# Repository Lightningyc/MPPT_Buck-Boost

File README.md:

&nbsp;&nbsp;

[English](./README.md)/中文

***
初赛演示视频：[2025年嵌入式设计大赛ST赛道-基于 STM32G4 平台的数控 MPPT 四开关 buckboost 变换器](https://www.bilibili.com/video/BV1HrGgzEE6s/)

# 作品实物图

# 1. 作品简介

## 1.1 关键性能指标
**输出电压：**
最高输出电压：10.74V

最低输出电压：15.20V

**稳态平均功率：**

12.39W

**稳态功率波动：**

0.02%

**最大功率点跟踪效率：**

94.8%
## 1.2 主要创新点

1. 双模式 MPPT 算法：结合 CV 法快速定位与 P&O 法动态跟踪，提高追
踪精度，加强了抗光照突变干扰能力。

2. 太阳能控制器硬件部分采用双板结构：控制板含 MCU 最小系统、采
样电路及调试接口；功率板集成主变换电路、驱动及滤波电路。全部设计基
于 KiCad 完成，兼顾调试便利与高低压隔离需求。

3. 使用 PSIM 仿真：充分利用 PSIM 仿真软件进行算法验证和参数优化，
实现了仿真与硬件开发的双线并行，提高了工作效率，还能提前发现潜在问
题，为后续硬件调试奠定了坚实基础。

# 2. 系统介绍

下图所示的太阳能控制器系统包含以下核心模块：DC-DC 电能变换电路、电压电流采样电路、输入输出滤波电路以及辅助电源电路。系统工作原理如下：

能量输入与处理：光伏电池板转换的太阳能电能，经输入滤波电路预处理后，输入至 DC-DC 变换电路。

状态监测：STM32G74 微控制器周期性采集经采样电路获取的输入/输出电压电流数据。

核心控制：微控制器对采集数据进行线性拟合，并运行内部 MPPT 算法，计算出控制指令。

功率调节：控制指令转化为PWM信号输出至栅极驱动器，驱动 DC-DC 变换电路的功率开关器件，从而动态调整其工作状态（如占空比），实现对输入或输出电参数的精准控制。

通信交互： 控制器通过 UART 接口与上位机软件 Vofa+ 通信，支持参数远程设定及实时运行数据（电压/电流）反馈。

安全保障与供电：

输入端设有防电流倒灌电路，防止能量逆向流动。

辅助电源电路集成提供 12V、5V 和 3.3V 的板级电源，为控制器内部所有模块稳定供电。

考虑到调试方便性以及高低压域分割问题，本文中的太阳能电池板控制器的硬件系统主要由控制部分与功率部分两块 PCB 板组合而成，其如图 2 所示，控制部分主要包括主控 MCU 最小系统、辅助电源、采样电路、调试接口和指示灯；功率部分主要包括电能变换主电路，输入输出滤波电路和栅极驱动电路。本作品的硬件全流程设计均基于 Kicad 软件。

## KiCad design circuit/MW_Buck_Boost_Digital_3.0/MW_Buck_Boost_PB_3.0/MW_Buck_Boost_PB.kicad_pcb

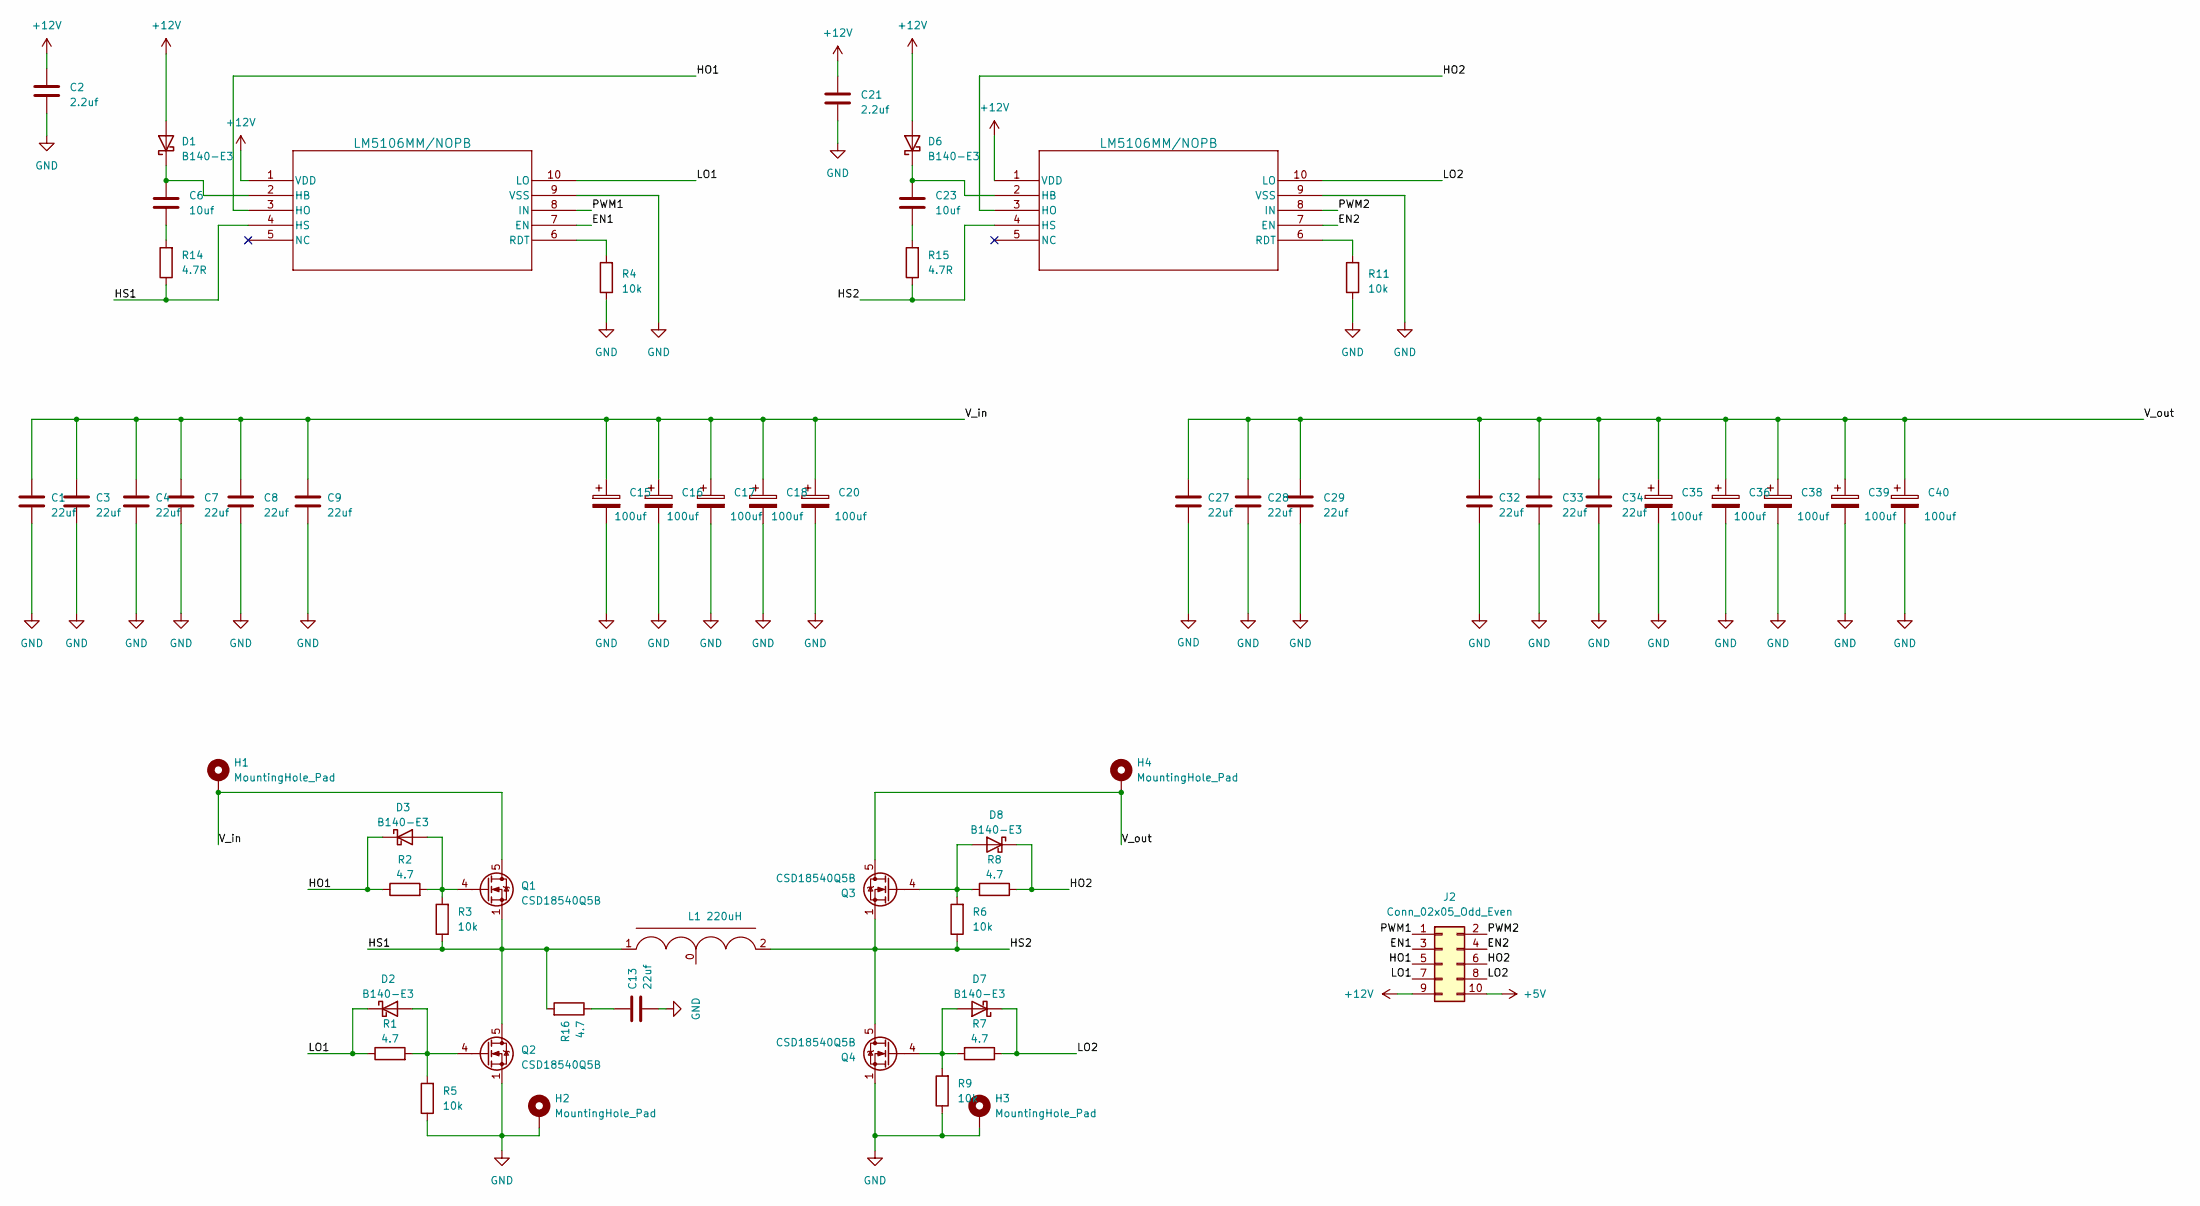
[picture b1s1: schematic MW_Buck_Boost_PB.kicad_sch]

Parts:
C1, C3, C4, C7, C8, C9, C13, C27, C28, C29, C32, C33, C34: 22uf; C_1206_3216Metric
C2, C21: 2.2uf; C_0603_1608Metric
C6, C23: 10uf; C_0603_1608Metric
C15, C16, C17, C18, C20, C35, C36, C38, C39, C40: 100uf; CP_Elec_8x10
D1, D2, D3, D6, D7, D8: B140-E3; D_SOD-123
H1, H2, H3, H4: MountingHole_Pad; MountingHole_3.2mm_M3_Pad_Via
J2: Conn_02x05_Odd_Even; PinHeader_2x05_P2.54mm_Vertical_SMD
L1: 220uH; L_Wurth_WE-HCFT-2012_LeadDiameter1.2mm
Q1, Q2, Q3, Q4: CSD18540Q5B; TDSON-8-1
R1, R2, R7, R8: 4.7; R_0603_1608Metric
R3, R4, R5, R6, R9, R11: 10k; R_0603_1608Metric
R14, R15: 4.7R; R_0603_1608Metric
R16: 4.7; R_1206_3216Metric
U1, U2: LM5106MM/NOPB; SOP50P490X110-10N

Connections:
+5V: J2.10
+12V: C2.1, C21.1, D1.2 (A), D6.2 (A), J2.9, U1.1 (VDD), U2.1 (VDD)
/EN1: J2.3, U1.7 (EN)
/EN2: J2.4, U2.7 (EN)
/HO1: D3.1 (K), J2.5, R2.1, U1.3 (HO)
/HO2: D8.1 (K), J2.6, R8.1, U2.3 (HO)
/HS1: L1.1, Q1.1 (S), Q1.2 (S), Q1.3 (S), Q2.5 (D), R3.1, R14.1, R16.2, U1.4 (HS)
/HS2: L1.2, Q3.1 (S), Q3.2 (S), Q3.3 (S), Q4.5 (D), R6.1, R15.1, U2.4 (HS)
/LO1: D2.1 (K), J2.7, R1.1, U1.10 (LO)
/LO2: D7.1 (K), J2.8, R7.1, U2.10 (LO)
/PWM1: J2.1, U1.8 (IN)
/PWM2: J2.2, U2.8 (IN)
/V_in: C1.1, C3.1, C4.1, C7.1, C8.1, C9.1, C15.1, C16.1, C17.1, C18.1, C20.1, H1.1, Q1.5 (D)
/V_out: C27.1, C28.1, C29.1, C32.1, C33.1, C34.1, C35.1, C36.1, C38.1, C39.1, C40.1, H4.1, Q3.5 (D)
GND: C1.2, C2.2, C3.2, C4.2, C7.2, C8.2, C9.2, C13.2, C15.2, C16.2, C17.2, C18.2, C20.2, C21.2, C27.2, C28.2, C29.2, C32.2, C33.2, C34.2, C35.2, C36.2, C38.2, C39.2, C40.2, H2.1, H3.1, Q2.1 (S), Q2.2 (S), Q2.3 (S), Q4.1 (S), Q4.2 (S), Q4.3 (S), R4.1, R5.1, R9.1, R11.1, U1.9 (VSS), U2.9 (VSS)
unnamed: C6.2, R14.2
unnamed: C13.1, R16.1
unnamed: C23.2, R15.2
unnamed: C6.1, D1.1 (K), U1.2 (HB)
unnamed: D2.2 (A), Q2.4 (G), R1.2, R5.2
unnamed: D3.2 (A), Q1.4 (G), R2.2, R3.2
unnamed: C23.1, D6.1 (K), U2.2 (HB)
unnamed: D7.2 (A), Q4.4 (G), R7.2, R9.2
unnamed: D8.2 (A), Q3.4 (G), R6.2, R8.2
unnamed: R4.2, U1.6 (RDT)
unnamed: R11.2, U2.6 (RDT)

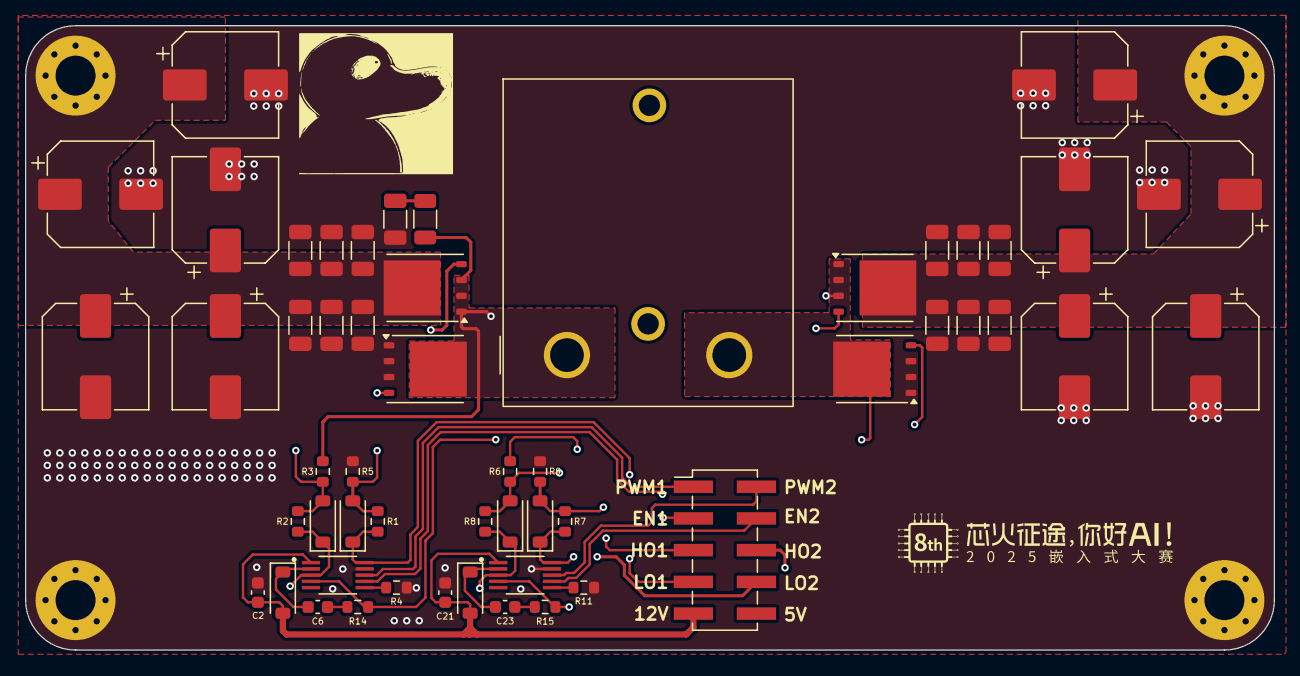
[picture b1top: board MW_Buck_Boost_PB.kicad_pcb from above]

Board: 4 copper layers, 100.0 x 50.0 mm, 58 parts (0 on the bottom side), 25 nets.

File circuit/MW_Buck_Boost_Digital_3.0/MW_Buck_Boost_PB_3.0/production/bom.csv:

Designator,Footprint,Quantity,Value,LCSC Part #
"C1, C13, C27, C28, C29, C3, C32, C33, C34, C4, C7, C8, C9",1206,13,22uf,
"C15, C16, C17, C18, C20, C35, C36, C38, C39, C40",CP_Elec_8x10,10,100uf,
"C2, C21",0603,2,2.2uf,
"C23, C6",0603,2,10uf,
"D1, D2, D3, D6, D7, D8",D_SOD-123,6,B140-E3,
"H1, H2, H3, H4",MountingHole_3.2mm_M3_Pad_Via,4,MountingHole_Pad,
J2,PinHeader_2x05_P2.54mm_Vertical_SMD,1,Conn_02x05_Odd_Even,
L1,L_Wurth_WE-HCFT-2012_LeadDiameter1.2mm,1,47uH,
"Q1, Q2, Q3, Q4",TDSON-8-1,4,CSD18540Q5B,
"R1, R2, R7, R8",0603,4,4.7,
"R11, R3, R4, R5, R6, R9",0603,6,10k,
"R14, R15",0603,2,4.7R,
R16,1206,1,4.7,
"U1, U2",SOP50P490X110-10N,2,LM5106MM/NOPB,

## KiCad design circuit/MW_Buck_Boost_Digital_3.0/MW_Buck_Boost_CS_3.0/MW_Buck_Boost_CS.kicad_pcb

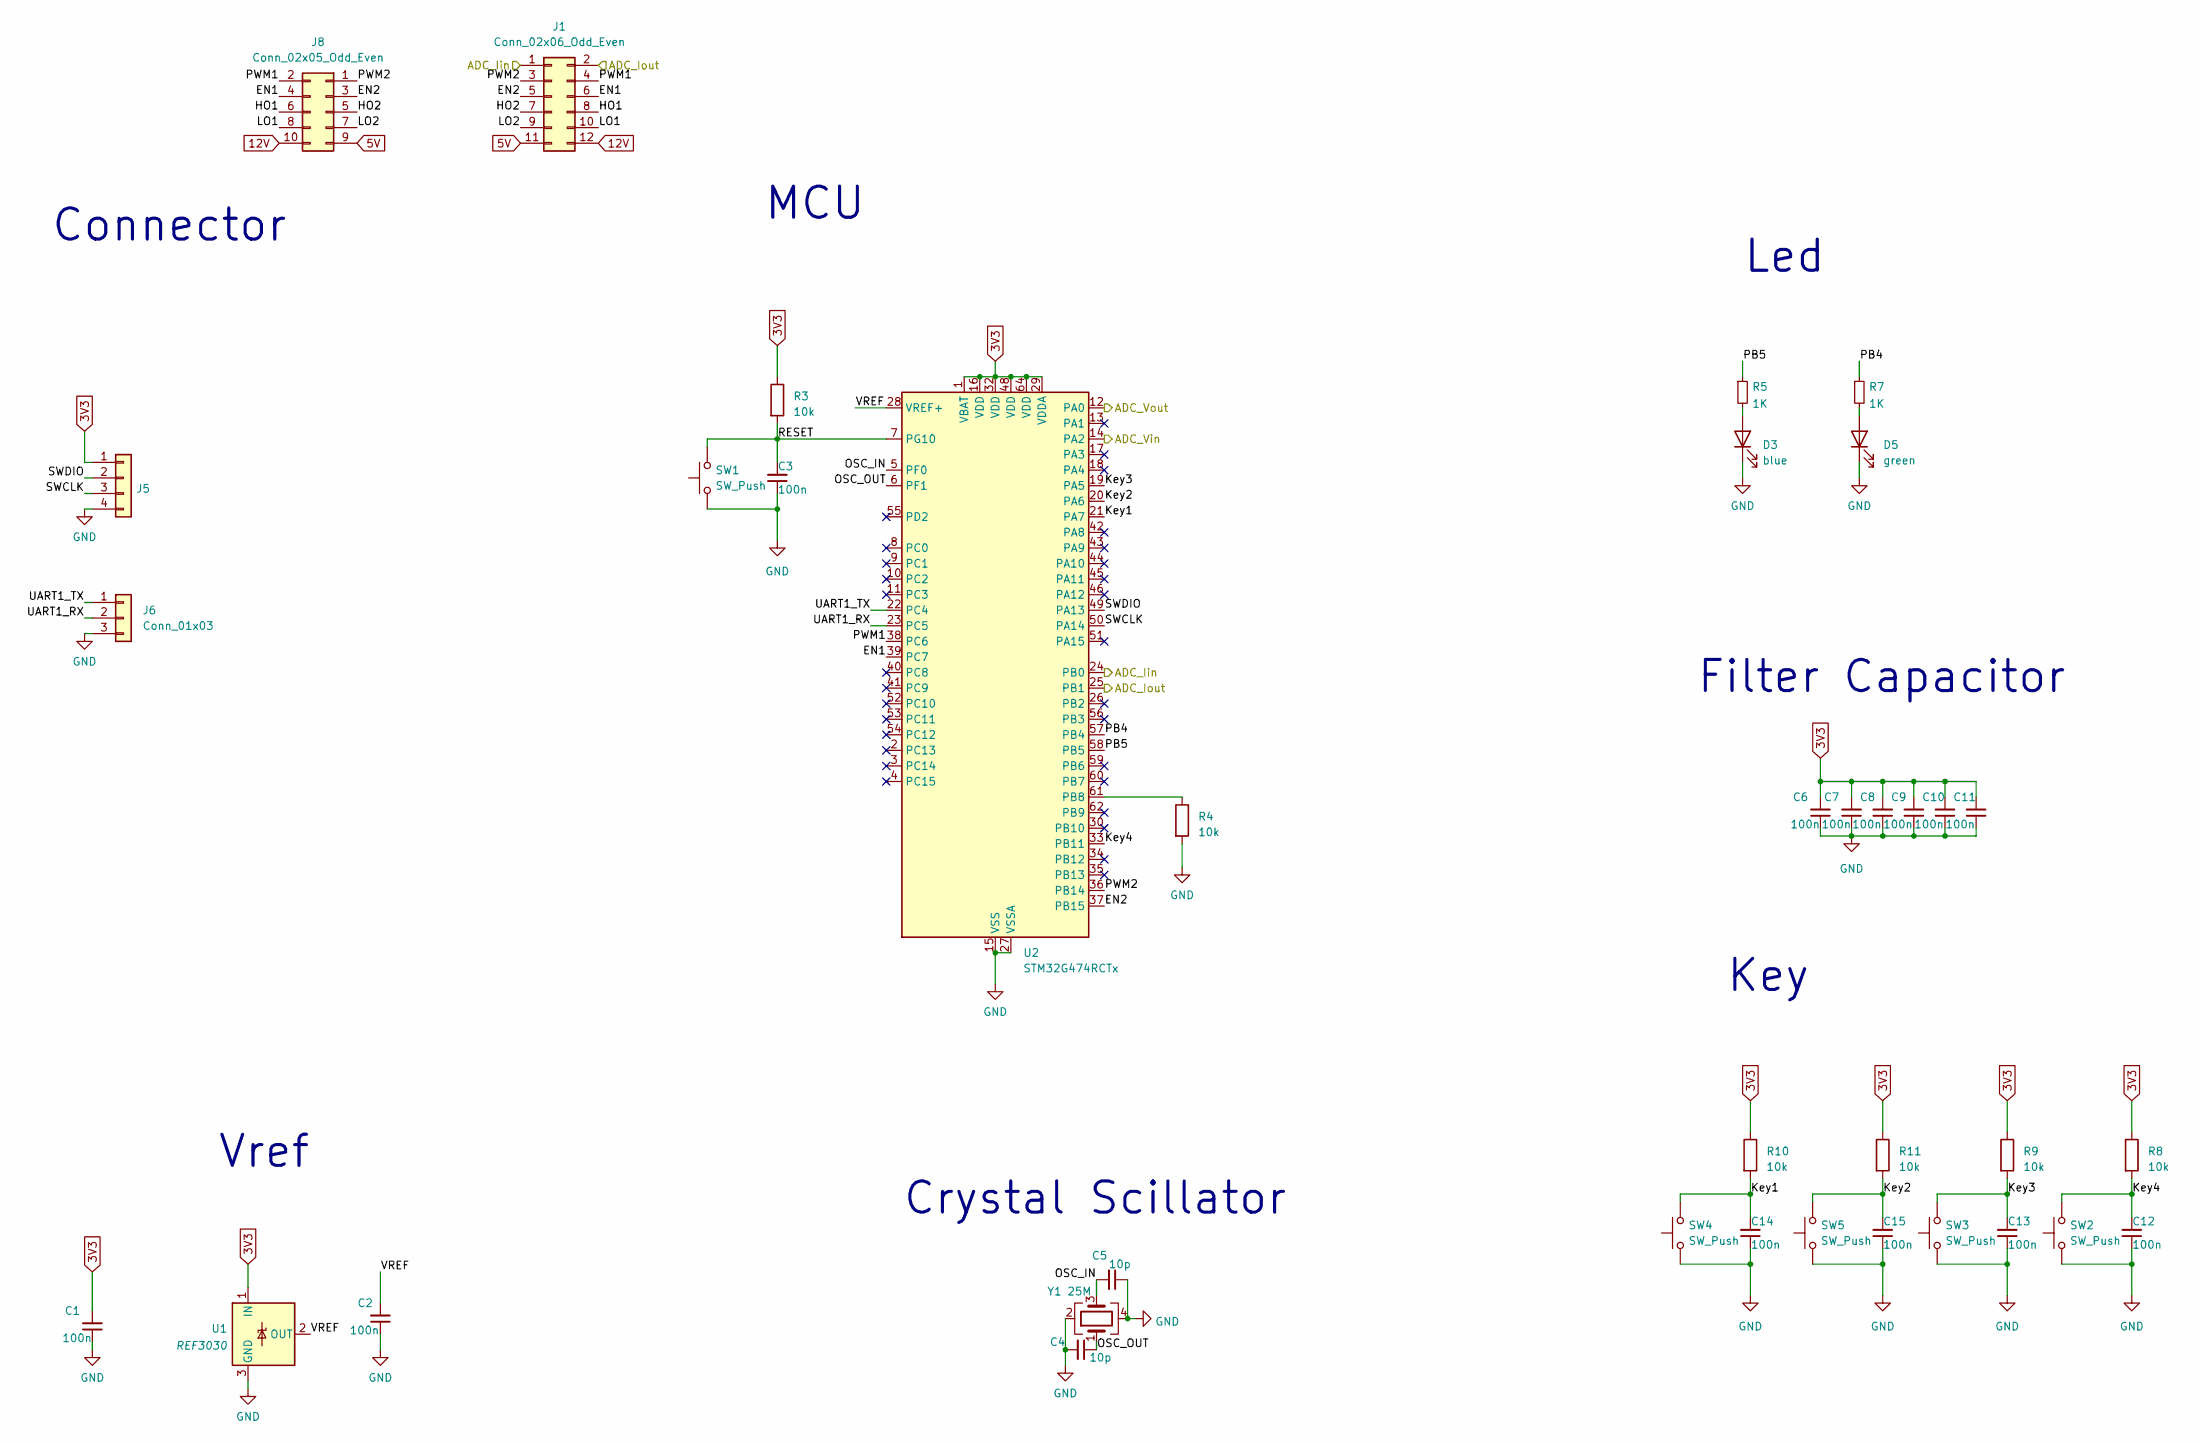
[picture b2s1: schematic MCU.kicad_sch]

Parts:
C1, C2, C3, C6, C7, C8, C9, C10, C11, C12, C13, C14, C15: 100n; C_0603_1608Metric_Pad1.08x0.95mm_HandSolder
C4, C5: 10p; C_0603_1608Metric_Pad1.08x0.95mm_HandSolder
D3: blue; LED_0603_1608Metric_Pad1.05x0.95mm_HandSolder
D5: green; LED_0603_1608Metric_Pad1.05x0.95mm_HandSolder
J1: Conn_02x06_Odd_Even; PinHeader_2x06_P2.54mm_Vertical_SMD
J5: Conn_01x04; JST_GH_SM04B-GHS-TB_1x04-1MP_P1.25mm_Horizontal
J6: Conn_01x03; JST_GH_SM03B-GHS-TB_1x03-1MP_P1.25mm_Horizontal
J8: Conn_02x05_Odd_Even; PinHeader_2x05_P2.54mm_Vertical_SMD
R3, R4, R8, R9, R10, R11: 10k; R_0603_1608Metric_Pad0.98x0.95mm_HandSolder
R5, R7: 1K; R_0603_1608Metric_Pad0.98x0.95mm_HandSolder
SW1, SW2, SW3, SW4, SW5: SW_Push; SW-SMD_4P-L4.2-W3.3-P2.15-LS5.1
U1: REF3030; SOT-23
U2: STM32G474RCTx; LQFP-64_10x10mm_P0.5mm
Y1: 25M; Crystal_SMD_3225-4Pin_3.2x2.5mm

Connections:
3V3: C1.2, C6.2, C7.2, C8.2, C9.2, C10.2, C11.2, J5.1, R3.1, R8.1, R9.1, R10.1, R11.1, U1.1 (IN), U2.1 (VBAT), U2.16 (VDD), U2.29 (VDDA), U2.32 (VDD), U2.48 (VDD), U2.64 (VDD); also elsewhere on the board
5V: J1.11, J8.9; also elsewhere on the board
12V: J1.12, J8.10; also elsewhere on the board
/MCU/ADC_Iin: J1.1, U2.24 (PB0); also elsewhere on the board
/MCU/ADC_Iout: J1.2, U2.25 (PB1); also elsewhere on the board
/MCU/ADC_Vin: U2.14 (PA2); also elsewhere on the board
/MCU/ADC_Vout: U2.12 (PA0); also elsewhere on the board
/MCU/EN1: J1.6, J8.4, U2.39 (PC7)
/MCU/EN2: J1.5, J8.3, U2.37 (PB15)
/MCU/HO1: J1.8, J8.6
/MCU/HO2: J1.7, J8.5
/MCU/Key1: C14.2, R10.2, SW4.2, U2.21 (PA7)
/MCU/Key2: C15.2, R11.2, SW5.2, U2.20 (PA6)
/MCU/Key3: C13.2, R9.2, SW3.2, U2.19 (PA5)
/MCU/Key4: C12.2, R8.2, SW2.2, U2.33 (PB11)
/MCU/LO1: J1.10, J8.8
/MCU/LO2: J1.9, J8.7
/MCU/OSC_IN: C5.2, U2.5 (PF0), Y1.3
/MCU/OSC_OUT: C4.1, U2.6 (PF1), Y1.1
/MCU/PB4: R7.1, U2.57 (PB4)
/MCU/PB5: R5.1, U2.58 (PB5)
/MCU/PWM1: J1.4, J8.2, U2.38 (PC6)
/MCU/PWM2: J1.3, J8.1, U2.36 (PB14)
/MCU/RESET: C3.2, R3.2, SW1.2, U2.7 (PG10)
/MCU/SWCLK: J5.3, U2.50 (PA14)
/MCU/SWDIO: J5.2, U2.49 (PA13)
/MCU/UART1_RX: J6.2, U2.23 (PC5)
/MCU/UART1_TX: J6.1, U2.22 (PC4)
/MCU/VREF: C2.2, U1.2 (OUT), U2.28 (VREF+)
GND: C1.1, C2.1, C3.1, C4.2, C5.1, C6.1, C7.1, C8.1, C9.1, C10.1, C11.1, C12.1, C13.1, C14.1, C15.1, D3.1 (K), D5.1 (K), J5.4, J6.3, R4.2, SW1.1, SW2.1, SW3.1, SW4.1, SW5.1, U1.3 (GND), U2.15 (VSS), U2.27 (VSSA), U2.31 (VSS), U2.47 (VSS), U2.63 (VSS), Y1.2, Y1.4; also elsewhere on the board
unnamed: D3.2 (A), R5.2
unnamed: D5.2 (A), R7.2
unnamed: R4.1, U2.61 (PB8)

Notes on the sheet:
Connector
Led
Vref
Crystal Scillator
MCU
Filter Capacitor
Key

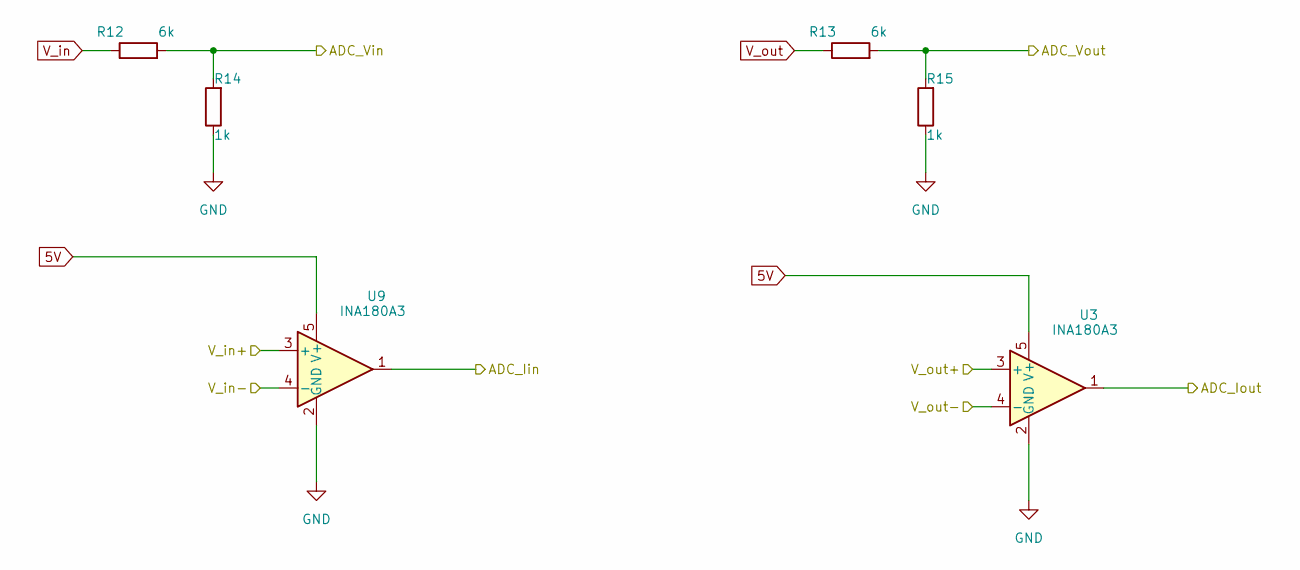
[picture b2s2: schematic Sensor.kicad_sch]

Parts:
R12, R13: 6k; R_0603_1608Metric_Pad0.98x0.95mm_HandSolder
R14, R15: 1k; R_0603_1608Metric_Pad0.98x0.95mm_HandSolder
U3, U9: INA180A3; SOT-23-5

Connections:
5V: U3.5 (V+), U9.5 (V+); also elsewhere on the board
/MCU/ADC_Iin: U9.1; also elsewhere on the board
/MCU/ADC_Iout: U3.1; also elsewhere on the board
/MCU/ADC_Vin: R12.2, R14.2; also elsewhere on the board
/MCU/ADC_Vout: R13.2, R15.2; also elsewhere on the board
/MainCircuit/V_in-: U9.4 (-); also elsewhere on the board
/MainCircuit/V_out+: U3.3 (+); also elsewhere on the board
GND: R14.1, R15.1, U3.2 (GND), U9.2 (GND); also elsewhere on the board
V_in: R12.1, U9.3 (+); also elsewhere on the board
V_out: R13.1, U3.4 (-); also elsewhere on the board

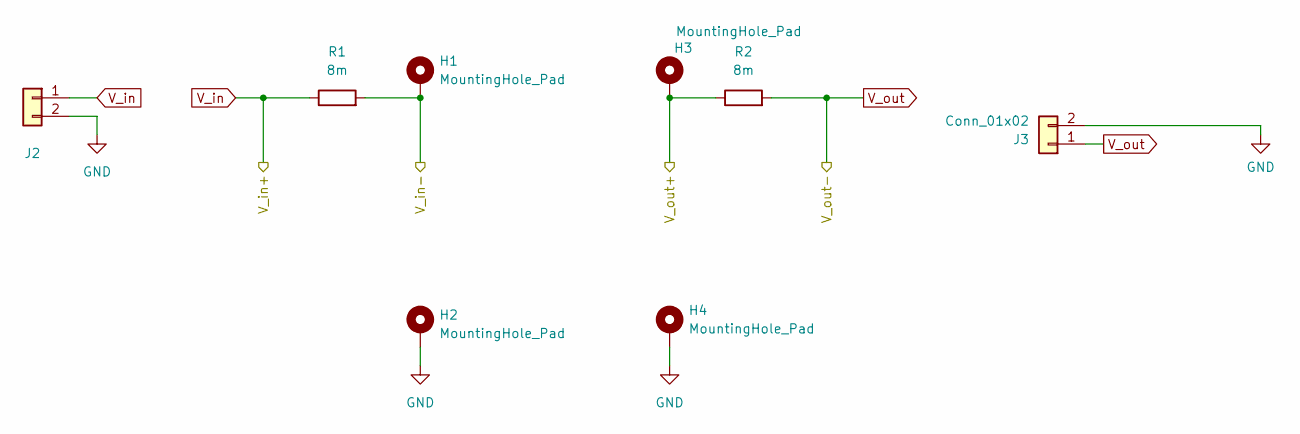
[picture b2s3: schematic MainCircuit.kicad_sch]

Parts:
H1, H2, H3, H4: MountingHole_Pad; MountingHole_3.2mm_M3_Pad_Via
J2: Conn_01x02; XT30PW-M
J3: Conn_01x02; XT30PW-F
R1, R2: 8m; Resistance

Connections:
/MainCircuit/V_in-: H1.1, R1.2; also elsewhere on the board
/MainCircuit/V_out+: H3.1, R2.1; also elsewhere on the board
GND: H2.1, H4.1, J2.2, J3.2; also elsewhere on the board
V_in: J2.1, R1.1; also elsewhere on the board
V_out: J3.1, R2.2; also elsewhere on the board

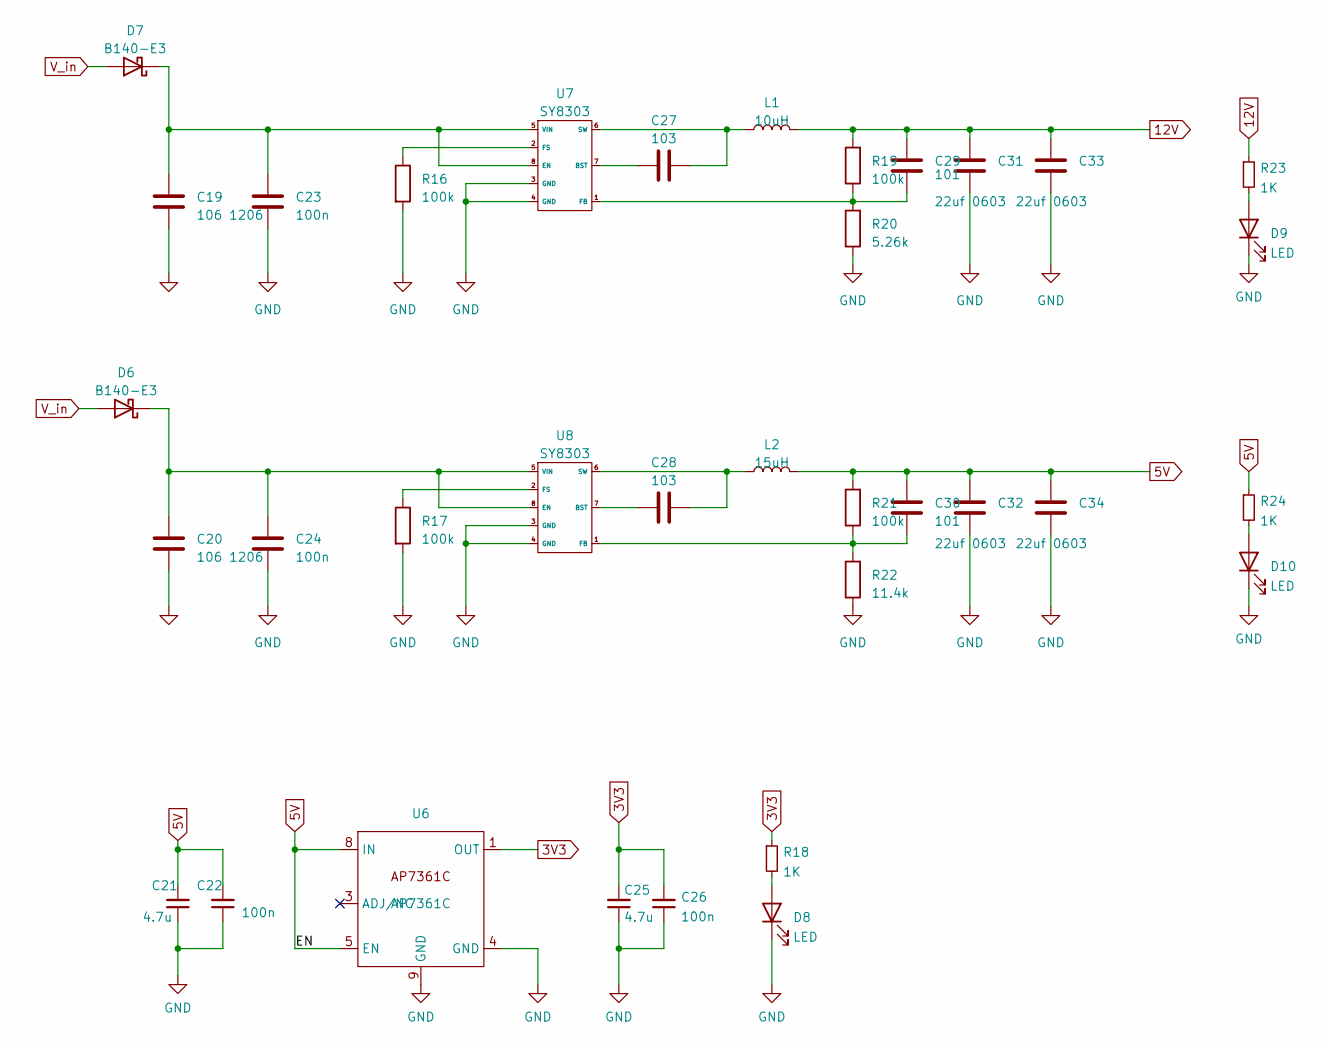
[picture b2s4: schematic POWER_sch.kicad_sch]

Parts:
C19, C20: 106 1206; C_1206_3216Metric_Pad1.33x1.80mm_HandSolder
C21, C25: 4.7u; C_0603_1608Metric_Pad1.08x0.95mm_HandSolder
C22, C23, C24, C26: 100n; C_0603_1608Metric_Pad1.08x0.95mm_HandSolder
C27, C28: 103; C_0603_1608Metric_Pad1.08x0.95mm_HandSolder
C29, C30: 101; C_0603_1608Metric_Pad1.08x0.95mm_HandSolder
C31, C32, C33, C34: 22uf 0603; C_1206_3216Metric_Pad1.33x1.80mm_HandSolder
D6, D7: B140-E3; D_SMA
D8, D9, D10: LED; LED_0603_1608Metric_Pad1.05x0.95mm_HandSolder
L1: 10uH; L_Abracon_ASPI-0630LR
L2: 15uH; L_Abracon_ASPI-0630LR
R16, R17, R19, R21: 100k; R_0603_1608Metric_Pad0.98x0.95mm_HandSolder
R18, R23, R24: 1K; R_0603_1608Metric_Pad0.98x0.95mm_HandSolder
R20: 5.26k; R_0603_1608Metric_Pad0.98x0.95mm_HandSolder
R22: 11.4k; R_0603_1608Metric_Pad0.98x0.95mm_HandSolder
U6: AP7361C; DFN-8-1EP_3x3mm_P0.65mm_EP1.55x2.4mm
U7, U8: SY8303; SOT-23-8

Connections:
3V3: C25.2, C26.2, R18.1, U6.1 (OUT); also elsewhere on the board
5V: C21.2, C22.2, C30.2, C32.2, C34.2, L2.2, R21.2, R24.1, U6.5 (EN), U6.8 (IN); also elsewhere on the board
12V: C29.2, C31.2, C33.2, L1.2, R19.2, R23.1; also elsewhere on the board
GND: C19.1, C20.1, C21.1, C22.1, C23.1, C24.1, C25.1, C26.1, C31.1, C32.1, C33.1, C34.1, D8.1 (K), D9.1 (K), D10.1 (K), R16.2, R17.2, R20.1, R22.1, U6.4 (GND), U6.9 (GND), U7.3 (GND), U7.4 (GND), U8.3 (GND), U8.4 (GND); also elsewhere on the board
unnamed: C20.2, C24.2, D6.1 (K), U8.5 (VIN), U8.8 (EN)
unnamed: C19.2, C23.2, D7.1 (K), U7.5 (VIN), U7.8 (EN)
unnamed: D8.2 (A), R18.2
unnamed: D9.2 (A), R23.2
unnamed: D10.2 (A), R24.2
unnamed: C27.1, U7.7 (BST)
unnamed: C29.1, R19.1, R20.2, U7.1 (FB)
unnamed: R16.1, U7.2 (FS)
unnamed: C27.2, L1.1, U7.6 (SW)
unnamed: C28.1, U8.7 (BST)
unnamed: C30.1, R21.1, R22.2, U8.1 (FB)
unnamed: R17.1, U8.2 (FS)
unnamed: C28.2, L2.1, U8.6 (SW)
V_in: D6.2 (A), D7.2 (A); also elsewhere on the board

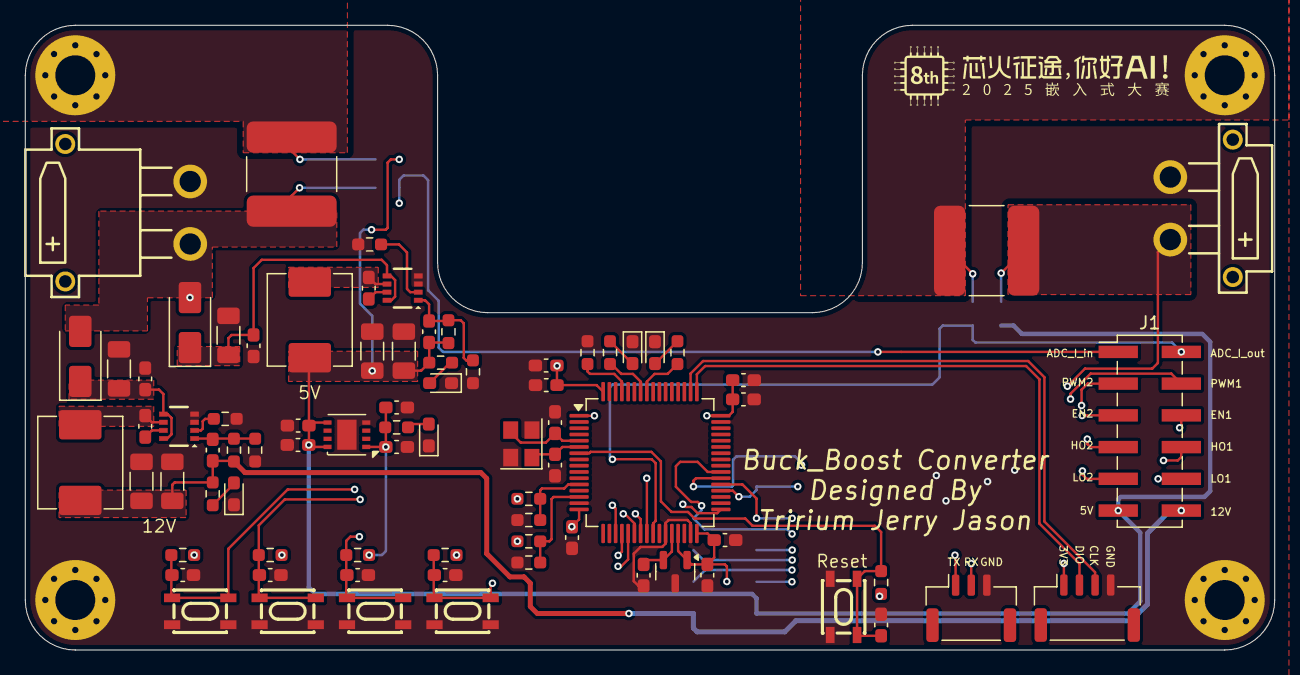
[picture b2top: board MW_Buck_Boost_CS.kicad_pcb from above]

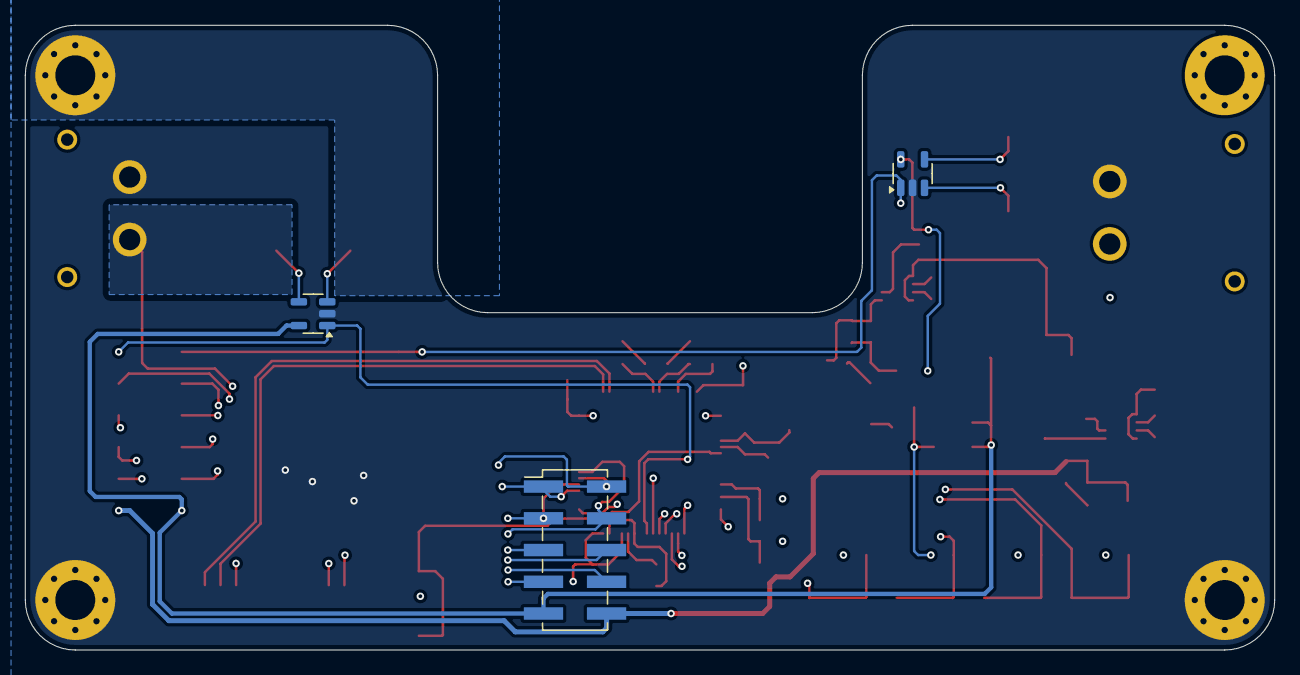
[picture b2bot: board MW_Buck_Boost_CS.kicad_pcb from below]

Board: 4 copper layers, 100.0 x 50.0 mm, 86 parts (3 on the bottom side), 50 nets.

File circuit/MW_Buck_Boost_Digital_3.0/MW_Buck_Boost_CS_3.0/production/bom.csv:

Designator,Footprint,Quantity,Value,LCSC Part #
"C1, C10, C11, C12, C13, C14, C15, C2, C22, C23, C24, C26, C3, C6, C7, C8, C9",0603,17,100n,
"C19, C20",1206,2,106 1206,
"C21, C25",0603,2,4.7u,
"C27, C28",0603,2,103,
"C29, C30",0603,2,101,
"C31, C32, C33, C34",1206,4,22uf 0603,
"C4, C5",0603,2,10p,
"D10, D8, D9",0603,3,LED,
D3,0603,1,blue,
D5,0603,1,green,
"D6, D7",D_SMA,2,B140-E3,
"H1, H2, H3, H4",MountingHole_3.2mm_M3_Pad_Via,4,MountingHole_Pad,
J1,PinHeader_2x06_P2.54mm_Vertical_SMD,1,Conn_02x06_Odd_Even,
J2,XT30PW-M,1,Conn_01x02,
J3,XT30PW-F,1,Conn_01x02,
J5,JST_GH_SM04B-GHS-TB_1x04-1MP_P1.25mm_Horizontal,1,Conn_01x04,
J6,JST_GH_SM03B-GHS-TB_1x03-1MP_P1.25mm_Horizontal,1,Conn_01x03,
J8,PinHeader_2x05_P2.54mm_Vertical_SMD,1,Conn_02x05_Odd_Even,
L1,L_Abracon_ASPI-0630LR,1,10uH,
L2,L_Abracon_ASPI-0630LR,1,15uH,
"R1, R2",Resistance,2,8m,
"R10, R11, R3, R4, R8, R9",0603,6,10k,
"R12, R13",0603,2,6k,
"R14, R15, R18, R23, R24, R5, R7",0603,7,1k,
"R16, R17, R19, R21",0603,4,100k,
R20,0603,1,5.26k,
R22,0603,1,11.4k,
"SW1, SW2, SW3, SW4, SW5",SW-SMD_4P-L4.2-W3.3-P2.15-LS5.1,5,SW_Push,
U1,SOT-23,1,REF3030,
U2,LQFP-64_10x10mm_P0.5mm,1,STM32G474RCTx,
"U3, U9",SOT-23-5,2,INA180A3,
U6,DFN-8-1EP_3x3mm_P0.65mm_EP1.55x2.4mm,1,AP7361C,
"U7, U8",SOT-23-8,2,SY8303,
Y1,Crystal_SMD_3225-4Pin_3.2x2.5mm,1,25M,

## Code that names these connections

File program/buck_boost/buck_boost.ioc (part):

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Mcu.Name=STM32G474R(B-C-E)Tx
Mcu.Package=LQFP64
Mcu.UserName=STM32G474RCTx
PA0.Mode=IN1-Single-Ended
PA0.Signal=ADC1_IN1
PA13.Mode=Serial_Wire
PA13.Signal=SYS_JTMS-SWDIO
PA14.Mode=Serial_Wire
PA14.Signal=SYS_JTCK-SWCLK
PA2.Mode=IN3-Single-Ended
PA2.Signal=ADC1_IN3
PB0.Mode=IN15-Single-Ended
PB0.Signal=ADC1_IN15
PB1.Mode=IN12-Single-Ended
PB1.Signal=ADC1_IN12
PB14.Mode=Output_TD1
PB14.Signal=HRTIM1_CHD1
PB15.Signal=GPIO_Output
PB4.GPIOParameters=GPIO_Speed,PinState,GPIO_PuPd,GPIO_ModeDefaultOutputPP
PB4.GPIO_ModeDefaultOutputPP=GPIO_MODE_OUTPUT_PP
PB4.GPIO_PuPd=GPIO_NOPULL
PB4.GPIO_Speed=GPIO_SPEED_FREQ_HIGH
PB4.PinState=GPIO_PIN_RESET
PB4.Signal=GPIO_Output
PB5.GPIOParameters=GPIO_Speed,PinState,GPIO_PuPd
PB5.GPIO_PuPd=GPIO_NOPULL
PB5.GPIO_Speed=GPIO_SPEED_FREQ_HIGH
PB5.PinState=GPIO_PIN_RESET
PB5.Signal=GPIO_Output
PB6.GPIOParameters=GPIO_Speed,PinState,GPIO_PuPd
PB6.GPIO_PuPd=GPIO_NOPULL
PB6.GPIO_Speed=GPIO_SPEED_FREQ_HIGH
PB6.PinState=GPIO_PIN_RESET
PB6.Signal=GPIO_Output
PC10.GPIOParameters=GPIO_Speed,PinState
PC10.GPIO_Speed=GPIO_SPEED_FREQ_HIGH
PC10.PinState=GPIO_PIN_SET
PC10.Signal=GPIO_Output
PC11.GPIOParameters=GPIO_Speed,PinState,GPIO_ModeDefaultOutputPP
PC11.GPIO_ModeDefaultOutputPP=GPIO_MODE_OUTPUT_PP
PC11.GPIO_Speed=GPIO_SPEED_FREQ_HIGH
PC11.PinState=GPIO_PIN_SET
PC11.Signal=GPIO_Output
PC4.Mode=Asynchronous
PC4.Signal=USART1_TX
PC5.Mode=Asynchronous
PC5.Signal=USART1_RX
PC6.Mode=Output_TF1
PC6.Signal=HRTIM1_CHF1
PC7.Signal=GPIO_Output
PF0-OSC_IN.Mode=HSE-External-Oscillator
PF0-OSC_IN.Signal=RCC_OSC_IN
PF1-OSC_OUT.Mode=HSE-External-Oscillator
PF1-OSC_OUT.Signal=RCC_OSC_OUT
RCC.HSE_VALUE=8000000
RCC.SYSCLKFreq_VALUE=170000000
RCC.SYSCLKSource=RCC_SYSCLKSOURCE_PLLCLK
board=custom

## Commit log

2025-07-10 fit the readme
